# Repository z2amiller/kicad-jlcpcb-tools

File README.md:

#  KiCAD JLCPCB tools

***

***

***

Plugin to generate all files necessary for JLCPCB board fabrication and assembly

- Gerber files
- Excellon files
- BOM file
- CPL file

Furthermore it lets you search the JLCPCB parts database and assign parts directly to the footprints which result in them being put into the BOM file.

On KiCad 10 boards with named [design variants](#design-variants-kicad-10),
compare and edit variants side by side and generate separate fabrication outputs.

## Installation 💾

### KiCAD PCM

Add my custom repo to *the Plugin and Content Manager*, the URL is:

```sh
https://raw.githubusercontent.com/Bouni/bouni-kicad-repository/main/repository.json
```

From there you can install the plugin via the GUI.

### Git

Clone this repo into your KiCad `scripting/plugins` folder.

> [!TIP]
> You can open the plugins directory directly from KiCad to avoid locating the path manually:
> In the *PCB Editor*, choose **Tools → External Plugins → Open Plugin Directory** (or **Reveal Plugin Folder in Finder** on macOS), or open **Preferences → PCB Editor → Action Plugins** and click the folder icon. From that directory, open a terminal and run `git clone https://github.com/Bouni/kicad-jlcpcb-tools.git`.

Alternatively, navigate to the folder in your terminal:

**Windows (Command Prompt)**

```cmd
cd "%USERPROFILE%\Documents\KiCad\<version>\scripting\plugins"
git clone https://github.com/Bouni/kicad-jlcpcb-tools.git
```

**Windows (PowerShell)**

```powershell
cd "$HOME\Documents\KiCad\<version>\scripting\plugins"
git clone https://github.com/Bouni/kicad-jlcpcb-tools.git
```

**Linux**

```sh
cd ~/.local/share/kicad/<version>/scripting/plugins
git clone https://github.com/Bouni/kicad-jlcpcb-tools.git
```

**macOS**

```sh
cd ~/Documents/KiCad/<version>/scripting/plugins
git clone https://github.com/Bouni/kicad-jlcpcb-tools.git
```

> [!NOTE]
> `<version>` can be `7.0`, `8.0`, `9.0`, or `X.YY` depending on the version you use. You may need to create the `scripting/plugins` folder if it does not exist.

After cloning, choose **Tools → External Plugins → Refresh Plugins** in the *PCB Editor* (or restart KiCad) to load the plugin.

### Flatpak :warning:

The Flatpak installation of KiCAD currently does not ship with pip and requests installed. The later is required for the plugin to work.
In order to get it working you can run the following 3 commands:

1. `flatpak run --command=sh org.kicad.KiCad`
2. `python -m ensurepip --upgrade`
3. `/var/data/python/bin/pip3 install requests`

See [issue #94](https://github.com/Bouni/kicad-jlcpcb-tools/issues/94) for more info.

## Usage 🥳

To access the plugin choose `Tools → External Plugins → JLCPCB Tools` from the *PCB Editor* menus

Checkout this screencast, it shows quickly how to use this plugin:

### Design variants (KiCad 10+)

Create named variants in KiCad and transfer them to the PCB to use the variant
table. Boards without named variants keep the ordinary parts table.

- **Compare variants side by side**, with Ref, Footprint, Side, PCB angle, and Correction columns fixed on the left when space permits. Ref stays fixed in narrower windows.
- **Spot differences quickly** through highlighted settings and yellow outlines around the affected variant’s cells in each component row.
- **Focus on differing component settings** with **Differences only** in the toolbar above the table.
- **Edit each variant independently:** Value, LCSC assignment, and BOM/POS/POP (populated) flags. Select components within one variant for batch assignments, flag changes, and copying.
- **Copy and paste selected components between variants:** Copy transfers Value, LCSC and BOM/POS/POP settings for every selected component; select the same components in another variant and Paste. Use **Copy cell value** for an individual value, or **Copy to variants…** to choose fields and destination variants.
- **Drag variant headers to reorder them** and bring variants together for comparison.
- **Compare price and stock availability** using compact indicators and hover details.
- **Choose an Output variant** to generate its BOM, placement, and fabrication files.
- **Review placement corrections for the Output variant** in the Correction column. Exact LCSC rules follow that variant's assigned part; pattern rules use Default's reference, Value, and placed footprint.

Assignments and flags are stored in the KiCad board; save the PCB to preserve edits.

The examples below use sample component data in the main JLCPCB Tools
window. Pointer and click cues make the actions easier to follow.

#### Edit settings and see differences

Change a setting in one variant to compare it with **Default**. Here,
turning off **POP** (populated) for **R4** in **Economy** highlights the
changed cell and outlines Economy’s cells in that row. The yellow outline
remains visible while the row is selected.

Turn POP back on to match Default and clear R4’s difference highlight.

#### Show differences only

Select **Differences only** in the toolbar above the table to focus on
differing component settings. In this example, enabling the checkbox
leaves **R1** and **R3** visible. Clear it to bring all five rows back.

#### Reorder variant columns

Drag a variant header to move its entire group of columns. Here,
**Premium** moves before **Economy**.

The translucent column preview follows the pointer, while the insertion
marker and **Drop before Economy** label show the destination. Release the
header to change the order to **Default**, **Premium**, **Economy**.

## Keyboard shortcuts

Windows can be closed with ctrl-w/ctrl-q/command-w/command-w (OS dependent) and escape.
Pressing enter in the keyword text box will start a search.

### Toggle BOM / CPL attributes

You can easily toggle the `exclude from BOM` and `exclude from CPL` attributes of one or multiple footprints.

### Select LCSC parts from the JLCPCB parts database

Select one or multiple footprints, click select part. You can select parts with equal value and footprint using the Select alike button.
In the upcoming modal dialog, search for parts, select the one of your choice and click select part.
The LCSC number of your selection will then be assigned to the footprints.

To type or paste an LCSC number instead, right-click the selected footprints and choose **Enter LCSC…**. It accepts a part number such as `C25804` or a product link copied from lcsc.com or jlcpcb.com. The number may be one the downloaded parts library does not list: JLC can still assemble LCSC-only parts it buys in through pre-order or global sourcing, and your library may be older than the part. The plugin asks once before assigning such a number. With no library downloaded there is nothing to check against, so it assigns without asking.

The part selector helps the same way: search for one LCSC number, and if the results don't show that exact part, a button beside the result count assigns it with one click.

### Automatic schematic saving

Closing JLCPCB Tools saves its LCSC assignments and supported BOM settings to
the project's schematics. The manual **Export to schematic** button has been
removed. On boards with design variants, this always saves **Default**;
selecting a named variant for fabrication does not change the schematic source.

A missing assignment field preserves the schematic's existing part number;
an explicit empty assignment clears it. Invalid or conflicting assignments are
preserved and reported while safe assignments still save. Footprints are linked
to symbols by KiCad's UUID paths, so changed or duplicate references do not
redirect a save. PCB-only footprints need no schematic update. Stale or ambiguous
links are preserved and reported.
For reused sheets, a shared field is updated only when every instance is linked
and agrees on that field. A linked multi-unit component updates all authenticated
units together; incomplete or ambiguous component membership is preserved.

Ordinary unassigned parts and PCB-only footprints close quietly. If an unassigned
PCB footprint has a part number in the schematic, use KiCad's **Update PCB from
Schematic** to transfer it to the board. This is an advisory, not a save failure.
When a conflict, invalid assignment, or unresolved link needs attention, the plugin keeps the complete report
at `jlcpcb/schematic-save-report.txt`, identifying affected footprints and the
reasons. Interactive closing also shows a warning; forced shutdown saves the
report without a prompt. A later complete save removes an outdated report.
Safe partial saves can complete; they do not authorize archival of active legacy
recovery data.

Projects that already have a `jlcpcb/project.db` see a one-time notice explaining
that the schematic is now the durable store. Before the first automatic write,
the plugin also keeps a permanent zip at
`jlcpcb/schematics-before-plugin-attributes.zip` so you can restore the previous
sheets if needed.

The plugin uses the project's associated schematics and preserves an `_old`
backup for each file it writes. Projects without an associated schematic close
without writing one. If a schematic is locked, the default **Cancel** keeps the
plugin open so you can close Schematic Editor and retry. **Save Anyway** approves
only the listed locks; **Close without saving** leaves the schematic unchanged.
Save errors also let you keep the window open or close without saving the
remaining changes. Earlier sheets may already have been saved if a later write
fails. A forced application shutdown cannot wait for these prompts: locked or
failed saves are logged and the window closes.

This saves schematic files. Use KiCad's PCB save command to persist changes to
the PCB itself. An already-open Schematic Editor does not reload exported files
automatically and can overwrite them if you choose **Save Anyway**.

### Where part assignments are stored

The live KiCad board is the sole source of LCSC assignments, with or without
named design variants. Selecting, pasting, or clearing a part updates the native
footprint fields or the selected variant's fields. **Save the PCB in KiCad to
persist these changes.** Refreshing the plugin reads the current board, including
edits made outside the plugin.

Both table modes recognize `LCSC`, `JLC`, and `JLCPCB` assignment fields,
optionally followed by `Part`, `Part Number`, `Part Num`, `Part No`, `PartNr`,
`PN`, `Number`, `Code`, or `ID`; case, spaces, and punctuation are ignored.
Conflicting or invalid assignments appear unassigned. Selecting or clearing a part updates
all recognized assignment fields together. Assignments and schematic saves preserve
existing alias names. A nonempty assignment creates a hidden `LCSC` field when no
recognized alias exists. Other prefixed fields, such as `JLCPCB Rotation` or
`LCSC custom code`, remain metadata; move part numbers from such fields into a
recognized assignment field.

*KiCad Symbol Properties with sample data for a 10k 0603 resistor (C25804).*

Previously, ordinary boards used database or CSV assignments while boards with
named variants read native fields. Editing or clearing Default, then removing
the last named variant, could therefore restore an obsolete database assignment.
Both modes now read and edit the board; the former schematic/database priority
setting no longer applies.

On opening, the plugin checks an existing `jlcpcb/project.db` for recoverable
legacy assignments before applying part preferences or displaying the initial
BOM. It imports a valid LCSC number only when the board assignment field is
missing and the reference, value, footprint, and BOM/POS flags exactly match
the historical row. Every linked schematic unit must also have no assignment or
the same part number. PCB-only footprints and projects confirmed to have no
schematic can recover directly into native fields, even if the PCB retains old
symbol paths. Unreadable project files and missing declared sheets do not count
as an absent schematic. KiCad 10's generated placeholder for a layout-only
project does not require a schematic file. Within a discovered hierarchy, stale
or ambiguous links remain unresolved.
Existing native values, explicit clears, invalid or conflicting
fields, unresolved links, and disagreeing shared instances are preserved.
Recovery imports neither stock nor flags and does not require a parts catalog.
Save the PCB to retain recovered assignments.

Once recovery is durable in the saved schematic or PCB, the active `part_info`
table is renamed to `part_info_retired`, preserving its rows and schema. Existing
archives remain intact; later archives use names such as `part_info_retired_2`.
The plugin rechecks the table's schema and data inside the archive transaction
so another window's changes cannot be archived using an outdated recovery check.
Before archival, the plugin reads the saved current PCB and sibling PCBs in the
same directory. macOS AppleDouble metadata sidecars are excluded. Recovery needed
by another board stays active, including recovery needed by temporary PCB copies.
The migration report names blocking sibling files and repeats only new notices;
acknowledgment does not allow archival. Obsolete rows can
be archived only when those saved boards confirm they are no longer needed;
an unsaved deletion or footprint change is insufficient. Native-only recovery
stays active until you explicitly save the PCB. The plugin never saves it for
you. Cancellation, incomplete saves, unresolved recovery, and unreadable saved
boards retain the recovery table for a later retry.

The durable `jlcpcb/legacy-migration-report.json` records the source board, old
legacy value, chosen native value or clear, and the reason for each recovery
decision, retaining original provenance and the latest board snapshot without
adding a full snapshot for every session. It survives schematic-report cleanup
and archival. When an existing native value or explicit clear supersedes a
legacy number, an interactive close
shows the previously unseen decisions once. Forced shutdown leaves that notice
pending for the next interactive close. Failed audit writes retain recovery data
and retry later without reapplying imported assignments. If the audit still cannot
be written, keep the plugin open to retry. Explicitly closing without the audit
or forcing shutdown can lose observations that could not be written to disk.

Archived assignments are never imported again, and legacy CSV files are never
automatically imported. Archival preserves generation counters, corrections,
other tables, and CSV files. Reading or refreshing assignments does not create
or modify `part_info`; the notice acknowledgment and generation counter use
the separate `metadata` table.

Supplier descriptions and other part details are cached in memory by LCSC
number and fetched again as needed. A part's assembly process and
Standard-only class are the exception: they are saved by LCSC number in
`global.db` in the data folder, so a board opened again shows them at once,
and they are fetched again in the background once they are 30 days old.
Stock and pricing come from the currently selected parts catalog; they are
not persisted as board assignments.

### Part preferences

Part preferences remember which LCSC part to use for a value and footprint combination across projects. Two independent settings are enabled by default:

- **Remember my part preferences** remembers each successful part selection or pasted LCSC assignment. The latest explicit assignment replaces the preference; opening a board does not change preferences.
- **Parts preferences fill in empty LCSC assignments** fills blank LCSC assignments once each time the plugin window opens. Existing assignments are preserved. DNP parts and parts excluded from BOM or POS are skipped.

Applying part preferences, including automatic filling on opening, writes the
native board fields. Save the PCB to keep those assignments.

Clearing an LCSC assignment keeps its part preference, so an eligible blank assignment may fill again on the next opening. Exclude the part or disable automatic filling to keep it blank. The right-click actions **Save part preferences** and **Apply part preferences** remain available even when automation is disabled. Use **Part preferences** to delete, import, or export preferences. Deleting a preference does not remove assignments from your boards.

### Generate fabrication data

Generate all necessary assembly files for your board with a simple click.

A new directory called `jlcpcb` is created, and in there, two separate folders are created, `gerber` and `production_files`.

In the gerber folder all necessary `*.gbr` and `*.drl` files are generated and zipped into the `production_files` folder, ready for upload to JLCPCB.
The zipfile is named `GERBER-<projectname>.zip`

Also in the `production_files` folder, two files are generated, `BOM-<projectname>.csv` and `CPL-<projectname>.csv`.

Footprints are included into the BOM and CPL files according to their `exclude from BOM` and `exclude from POS` attributes.

A footprint's CPL `Mid X`/`Mid Y` is the center of the bounding box of its soldered pads: NPTH holes and paste-only pads are left out, and a footprint without soldered pads uses its own position.

Optional pre/post generation hook scripts can be configured in settings.

- The pre-hook runs before generation and can block generation on failure (with Continue/Cancel prompt).
- The post-hook runs only after successful generation.

See [HOOKS.md](HOOKS.md) for configuration details and available environment variables.

### Export Additional JLC Specific Layers

Some boards you have manufactured will require additional layers in your Gerber. For example, when manufacturing flex PCBs with a stiffener, JLC requires a layer outlining the stiffener layer (top/bottom), dimensions and the stiffener material properties (material, thickness etc). Export these additional JLC specific layers in your production files with a simple modification.

Additional layers can be exported by creating layers with `JLC_` as the prefix of the layer name. You can access and edit the layer names in *Board Setup/Board Stackup/Board Editor Layers*

This tool will automatically export all additional layers with the JLC_ prefix and add them to the production files in `GERBER-<projectname>.zip`

## Footprint rotation correction

JLCPCB seems to need corrected rotation information. @matthewlai implemented that in his [JLCKicadTools](https://github.com/matthewlai/JLCKicadTools) and I adopted his work in this plugin as well.
You can download Matthews file from GitHub and manage your own corrections in the Rotation manager.

See [Importing and repairing corrections](CORRECTIONS.md) for supported CSV
formats, validation rules, and recovery of invalid records from older versions.

## Icons

This plugin makes use of a lot of icons from the excellent [Material Design Icons](https://materialdesignicons.com/)

## Development

1. Fork repo
2. Git clone forked repo
3. Install pre-commit `pip install pre-commit`
4. Setup pre-commit `pre-commit run`
5. Create feature branch `git switch -c my-awesome-feature`
6. Make your changes
7. Commit your changes `git commit -m "Awesome new feature"`
8. Push to GitHub `git push`
9. Create PR

Make sure you make use of pre-commit hooks in order to format everything nicely with `black`
In the near future I'll add `ruff` / `pylint` and possibly other pre-commit-hooks that enforce nice and clean code style.

### Tests

Report ordinary Python tests, real wx controls, and real KiCad tests separately.
A passing test that uses a fake board does not verify KiCad's file handling,
project state, or native object cleanup.

```sh
python -m pytest -rs -m 'not native_wx and not native_kicad'
python -m pytest -rs --require-native=wx -m 'not native_kicad and not os_input'
python -m pytest -rs --require-native=wx -m os_input
python -m pytest -rs --require-native=kicad -m native_kicad
```

The required native modes reject missing libraries, empty native selections, and
skipped native tests. The KiCad mode accepts two skips: tests of design variants on
a KiCad without them, and the forced-DRC test on KiCad 10, whose DRC crashes
outside KiCad. Run them with Python libraries matching the installed KiCad
or wx packages. Mouse/keyboard tests require an isolated desktop with a window
manager; Linux native tests can use Xvfb.

To reproduce CI locally, use an Ubuntu 24.04 Docker container with the same CPU
architecture, KiCad packages, dependencies, and commands as
[the test workflow](.github/workflows/tests.yml). Copy the tracked source tree so
untracked test files cannot change collection. Include the tested revision,
Python/wx/KiCad versions, command, and pass/skip/deselection counts when reporting
results. A required lane that was not run remains unvalidated.

### Settings

`default_settings.json` holds the settings a fresh install starts from and is the only
settings file tracked in git. The plugin writes the settings you actually use to
`settings.json` beside it, which is git-ignored, so toggling a checkbox while developing
no longer shows up as a change to commit.

On every launch the stored settings are layered over the defaults, so a setting added by
a newer version arrives with its default rather than being missing. Add new settings to
`default_settings.json`; `tests/test_settings_defaults.py` fails if a setting the code
reads has no default shipped for it.

## How to rebuild the parts database

The parts database is rebuilt by the [update_parts_database.yml GitHub workflow](https://github.com/Bouni/kicad-jlcpcb-tools/blob/main/.github/workflows/update_parts_database.yml)

You can reference the steps in the 'Update database' section for the commands to run locally.

## python libraries

lib/ contains the necessary python packages that may not be a part of the KiCad python distribution.

These packages include:

- packaging

To install a package, such as 'packaging':

```python
pip install packaging --target ./lib
```

To update these packages:

```python
pip install packaging --upgrade --target ./lib
```

Future versions of KiCad may have support for a requires.txt to automate this process.

## Standalone mode

Allows the plugin UI to be started without KiCAD, enabling debugging with an IDE like pycharm / vscode.

Standalone mode is under development.

### Limitations

- All board / footprint / value data are hardcoded stubs, see standalone_impl.py

### How to use

To use the plugin in standlone mode you'll need to identify three pieces of information specific to your Kicad version, plugin path, and OS.

#### Python

The <i><b>{KiCad python}</b></i> should be used, this can be found at different locations depending on your system:

| OS     | Kicad python                                                                                |
|--------|---------------------------------------------------------------------------------------------|
|Mac     | /Applications/KiCad/KiCad.app/Contents/Frameworks/Python.framework/Versions/3.9/bin/python3 |
|Linux   | /usr/bin/python3                                                                            |
|Windows | C:\Program Files\KiCad\8.0\bin\python.exe                                                   |

#### Working directory

The <i><b>{working directory}</b></i> should be your plugins directory, ie:

| OS     | Working dir                                                |
|--------|------------------------------------------------------------|
|Mac     | ~/Documents/KiCad/<version>/scripting/plugins/             |
|Linux   | ~/.local/share/kicad/<version>/scripting/plugins/          |
|Windows | %USERPROFILE%\Documents\KiCad\<version>\scripting\plugins\ |

> [!NOTE]  
> <version> can be 7.0, 8.0, 9.0, or X.YY depending on the version you use

#### Plugin folder name

The <i><b>{kicad-jlcpcb-tools folder name}</b></i> should be the name of the kicad-jlcpcb-tools folder.

- For Kicad managed plugins this may be like

> com_github_bouni_kicad-jlcpcb-tools

- If you are developing kicad-jlcpcb-tools this is the folder you cloned the kicad-jlcpcb-tools as.

#### Command line

- Change to the working directory as noted above
- Run the python interpreter with the <i><b>{kicad-jlcpcb-tools folder name}</b></i> folder as a module.

For example:

```sh
cd {working directory}
{kicad_python} -m {kicad-jlcpcb-tools folder name}
```

For example on Mac:

```sh
/Applications/KiCad/KiCad.app/Contents/Frameworks/Python.framework/Versions/3.9/bin/python3 -m kicad-jlcpcb-tools
```

For example on Linux:

```sh
cd ~/.local/share/kicad/8.0/scripting/plugins/ && python -m kicad-jlcpcb-tools
```

For example on Windows:

```cmd
& 'C:\Program Files\KiCad\8.0\bin\python.exe' -m kicad-jlcpcb-tools
```

#### IDE

- Configure the command line to be '{kicad_python} -m {kicad-jlcpcb-tools folder name}'
- Set the working directory to {working directory}

If using PyCharm or Jetbrains IDEs, set the interpreter to Kicad's python, <i><b>{Kicad python}</b></i> and under 'run configuration' select Python.

Click on 'script path' and change instead to 'module name',
entering the name of the kicad-jlcpcb-tools folder, <i><b>{kicad-jlcpcb-tools folder name}</b></i>.

## How to release new versions of this plugin

[bouni-kicad-repository](https://raw.githubusercontent.com/Bouni/bouni-kicad-repository/main/repository.json) contains the
files for the latest version of the plugin, in the format KiCAD expects from external plugins.

To release a new version of this plugin:

1. In the <b>kicad-jlcpcb-plugin</b> repository:
   1. Visit the releases page 
   1. Click on 'Choose a tag', enter the next release number, say 2025.04.01 for example, and click on 'Create Tag' 
   1. Click 'Generate release notes' 
   1. If the release notes looks good, click on 'Publish release' 
1. Automatically the new release will trigger the 'kicad-pcm' workflow which will:
   1. Pull the latest plugin tag
   1. Create the appropriate pcm archive
   1. Upload the zip as an asset to a new GitHub release
   1. benc-uk/workflow-dispatch@v1 is used to trigger the 'Rebuild repository' workflow in [bouni-kicad-repository](https://github.com/Bouni/bouni-kicad-repository)
1. Automatically in the <b>bouni-kicad-repository</b>, the 'Rebuild repository' (rebuild.yml) workflow runs 'generate.py'
   1. generate.py updates .json and the latest .zip file using the release assets from the kicad-jlcpcb-plugin repository
1. The plugin should now be visible to users via the plugin manager.

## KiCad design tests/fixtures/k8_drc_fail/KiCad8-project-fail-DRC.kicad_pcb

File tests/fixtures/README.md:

# KiCad SWIG integration fixtures

This folder holds small board fixtures used by `pytest -m kicad_integration`.

## Fixture goals

- Keep fixtures small and quick to parse in CI.
- Prefer representative real-world examples when practical.
- Include one intentionally DRC-failing board for stable-path/category assertions.

## Version compatibility policy

- Primary compatibility test direction: **KiCad 8 board opened in KiCad 9 runtime**.
- Reverse compatibility (KiCad 9 board in KiCad 8 runtime) is not required.

## Suggested fixture set

- `k9_smoke_ok/` – small KiCad 9 board that loads cleanly.
- `k9_drc_fail/` – small KiCad 9 board with intentional DRC issues.
- `k8_compat_ok/` – KiCad 8 board expected to open in KiCad 9 runtime.

## Current checked-in fixtures

- `k9_smoke_ok/fx-Full125B.kicad_pcb` – initial real-world KiCad 9 smoke fixture.
- `k9_drc_fail/Normal125B-DRCFail.kicad_pcb` – real-world KiCad 9 fixture intended to fail DRC.
- `k8_compat_ok/KiCad8-project.kicad_pcb` – KiCad 8 board for open-in-KiCad-9 compatibility checks.
- `k8_drc_fail/KiCad8-project-fail-DRC.kicad_pcb` – KiCad 8 board intended to fail DRC checks.
- `k10_smoke_ok/util-curvetracer.kicad_pcb` – KiCad 10 smoke fixture (native KiCad 10 runtime).
- `k10_drc_fail/util-curvetracer-fail-drc.kicad_pcb` – KiCad 10 DRC-fail fixture.

Fixture metadata is tracked in `tests/fixtures/manifest.json` and consumed by integration tests.

### Manifest conventions

- `intent: "smoke_ok"` for basic load/enumeration fixtures.
- `intent: "compat_open_in_k9"` for cross-version open tests (e.g. KiCad 8 -> KiCad 9).
- `intent: "drc_fail"` for intentional DRC-failing fixtures.
- `expected_drc_patterns` can optionally list stable substrings that should appear in parsed DRC error messages.
- `min_runtime_major` / `max_runtime_major` can constrain fixtures to matching KiCad runtimes.

### DRC integration execution

DRC integration checks are opt-in by default. Enable them with:

```sh
KICAD_DRC_INTEGRATION=1 pytest -m kicad_integration tests/test_kicad_swig_integration.py
```

## Notes

- Store only non-sensitive board data.
- Keep external dependencies out of fixture projects where possible.
- If exact DRC violation counts drift by KiCad version, tests should assert stable categories/paths instead of exact totals.

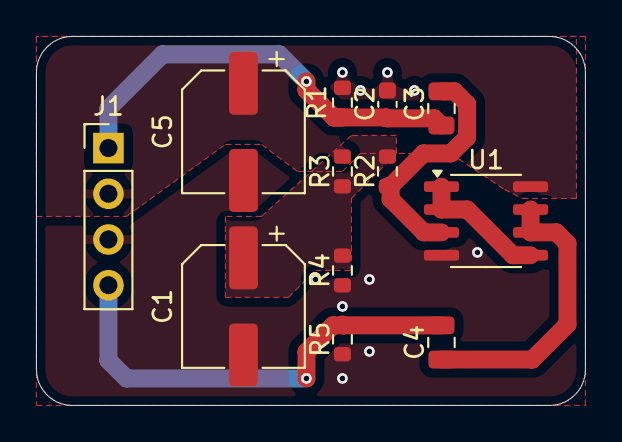
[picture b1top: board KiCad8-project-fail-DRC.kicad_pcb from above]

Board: 2 copper layers, 30.5 x 20.5 mm, 12 parts (0 on the bottom side), 8 nets.

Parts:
C1, C5: 100uF; CP_Elec_6.3x4.5
C2: 100pF; C_0603_1608Metric
C3: 100nF; C_0805_2012Metric
C4: 1uF; C_0805_2012Metric
J1: Conn_01x04_Pin; PinHeader_1x04_P2.54mm_Vertical
R1: 2.2M; R_0603_1608Metric
R2: 470K; R_0603_1608Metric
R3, R4: 47K; R_0603_1608Metric
R5: 100K; R_0603_1608Metric
U1: TL072; SOIC-8_3.9x4.9mm_P1.27mm

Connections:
+9V: C5.1, J1.2, R3.1, U1.8 (V+)
GND: C1.2, C2.2, C5.2, J1.3, R1.2, R4.2, R5.2, U1.4 (V-)
IN: C2.1, C3.2, J1.1, R1.1
unnamed: C3.1, R2.2, U1.3 (+)
unnamed: U1.1, U1.2 (-), U1.5 (+)
unnamed: C4.2, U1.6 (-), U1.7
OUT: C4.1, J1.4, R5.1
VREF: C1.1, R2.1, R3.2, R4.1

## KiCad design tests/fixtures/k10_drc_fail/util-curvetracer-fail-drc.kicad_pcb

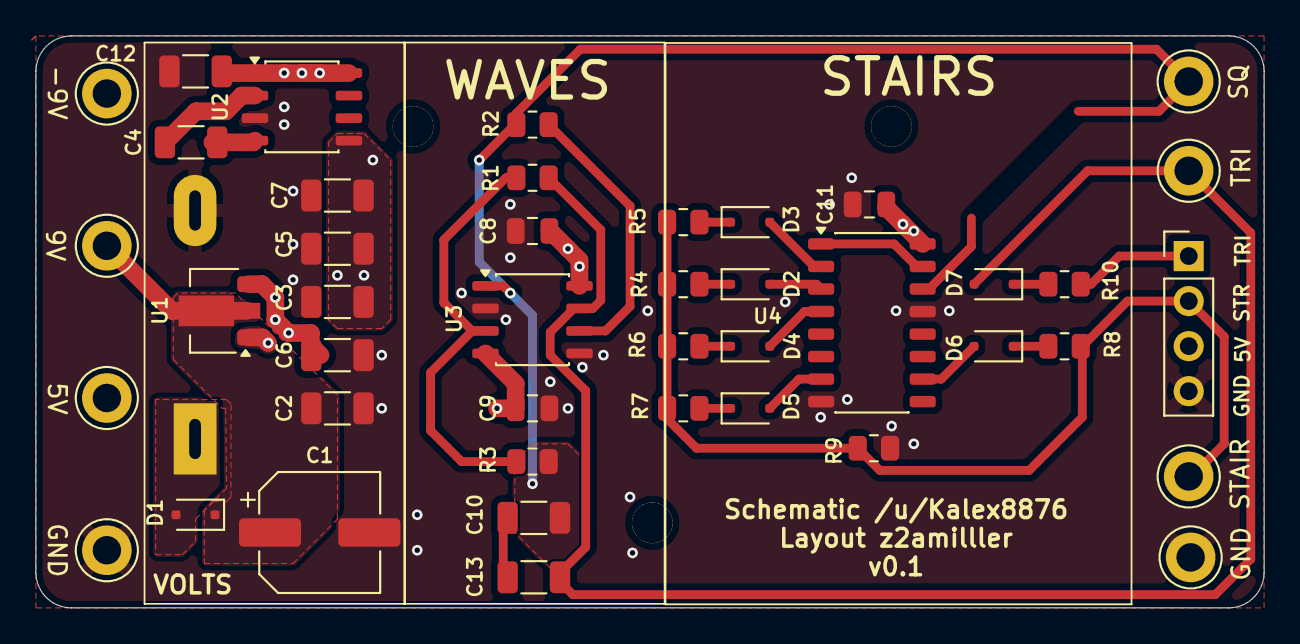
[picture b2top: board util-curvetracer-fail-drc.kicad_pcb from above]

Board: 4 copper layers, 69.2 x 32.2 mm, 44 parts (1 on the bottom side), 26 nets.

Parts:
BT1: Battery_Cell; BatteryHolder_MPD_BA9VPC_1xPP3
C1: 100uF; CP_Elec_6.3x5.4
C2, C3, C4, C5, C6, C7, C10, C12, C13: 10uF; C_1206_3216Metric
C8, C9, C11: 1uF; C_0805_2012Metric
D1: 1N5819; D_SOD-323F
D2, D3, D4, D5, D6, D7: 5S30; D_SOD-323F
J1: Conn_01x04_Socket; PinHeader_1x04_P2.54mm_Vertical
R1: 10K; R_0805_2012Metric
R2, R7, R10: 1K; R_0805_2012Metric
R3: 20K; R_0805_2012Metric
R4: 7.5K; R_0805_2012Metric
R5: 3.6K; R_0805_2012Metric
R6: 1.8K; R_0805_2012Metric
R8: 560R; R_0805_2012Metric
R9: 1.2K; R_0805_2012Metric
TP1: 9V; TestPoint_Keystone_5010-5014_Multipurpose
TP2: 5V; TestPoint_Keystone_5010-5014_Multipurpose
TP3, TP8: GND; TestPoint_Keystone_5010-5014_Multipurpose
TP4: -9V; TestPoint_Keystone_5010-5014_Multipurpose
TP5: SQ; TestPoint_Keystone_5010-5014_Multipurpose
TP6: TRI; TestPoint_Keystone_5010-5014_Multipurpose
TP7: STAIR; TestPoint_Keystone_5010-5014_Multipurpose
U1: HT75xx-1-SOT89; SOT-89-3
U2: LTC1044; JEITA_SOIC-8_3.9x4.9mm_P1.27mm
U3: TL072; JEITA_SOIC-8_3.9x4.9mm_P1.27mm
U4: 4017; JEITA_SOIC-16_3.9x9.9mm_P1.27mm

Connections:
+5V: C3.1, C11.1, J1.3, TP2.1 (1_1), U1.3 (VOUT), U4.16 (VDD)
+9V: BT1.1 (+), D1.2 (A)
+9VA: C1.1, C2.1, C8.1, C12.1, D1.1 (K), TP1.1 (1_1), U1.2 (VIN), U2.1 (BOOST), U2.8 (V+), U3.8 (V+)
-9V: C5.1, C6.1, C7.1, C9.2, TP4.1 (1_1), U2.5 (VOUT), U3.4 (V-)
GND: BT1.2 (-), C1.2, C2.2, C3.2, C5.2, C6.2, C7.2, C8.2, C9.1, C11.2, C12.2, J1.4, R9.2, TP3.1 (1_1), TP8.1 (1_1), U1.1 (GND), U2.3 (GND), U3.2 (-), U3.5 (+), U4.8 (VSS), U4.13 (CKEN)
unnamed: C10.1, C13.2
unnamed: D2.2 (A), U4.3 (Q0)
unnamed: D2.1 (K), R4.1
unnamed: D3.2 (A), U4.2 (Q1)
unnamed: D3.1 (K), R5.1
unnamed: D4.2 (A), U4.4 (Q2)
unnamed: D4.1 (K), R6.1
unnamed: D5.2 (A), U4.7 (Q3)
unnamed: D5.1 (K), R7.1
unnamed: D6.2 (A), U4.10 (Q4)
unnamed: D6.1 (K), R8.1
unnamed: D7.1 (K), R10.2
unnamed: J1.1, R10.1
unnamed: C4.1, U2.2 (CAP+)
unnamed: C4.2, U2.4 (CAP-)
unnamed: R1.2, R3.2, U3.3 (+)
unnamed: R2.1, U3.6 (-)
unnamed: U4.1 (Q5), U4.15 (Reset)
SQUARE: C10.2, R2.2, R3.1, TP5.1 (1_1), U3.1, U4.14 (CLK)
STAIRCASE: J1.2, R4.2, R5.2, R6.2, R7.2, R8.2, R9.1, TP7.1 (1_1)
TRIANGLE: C13.1, D7.2 (A), R1.1, TP6.1 (1_1), U3.7

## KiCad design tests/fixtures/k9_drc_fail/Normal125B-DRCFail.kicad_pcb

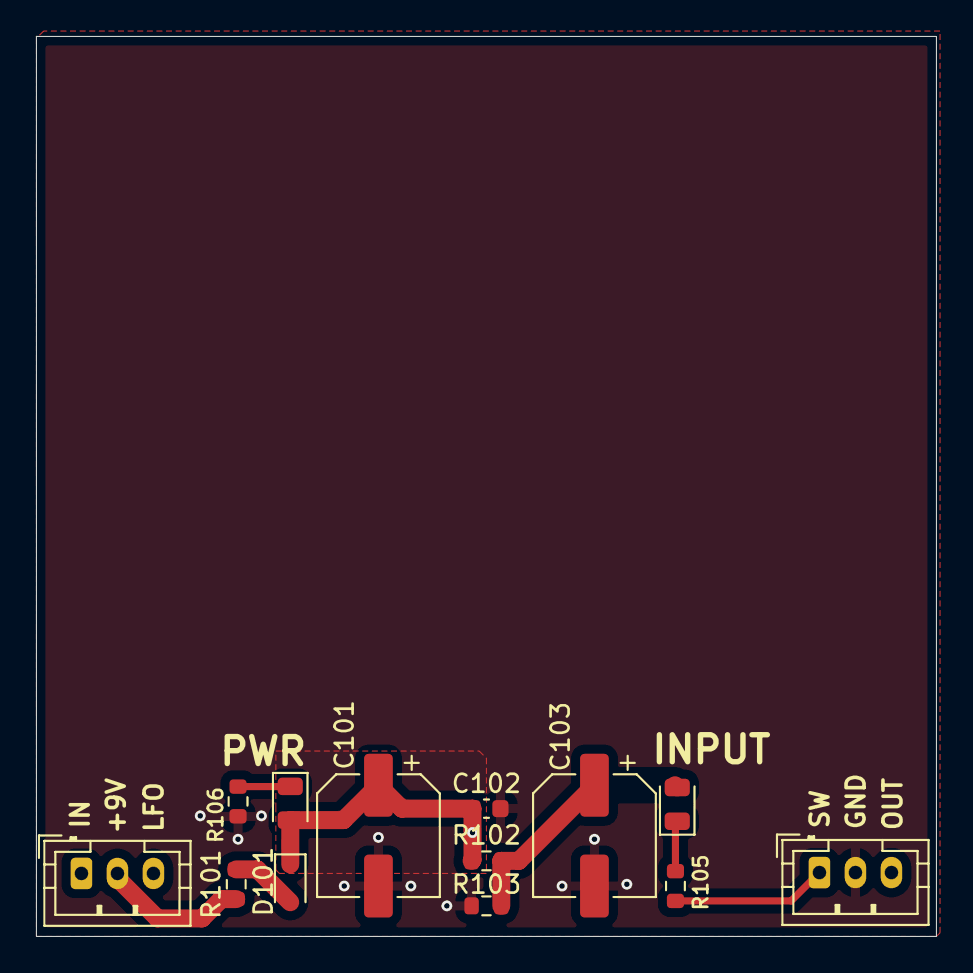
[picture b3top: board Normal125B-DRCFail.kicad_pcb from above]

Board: 2 copper layers, 50.0 x 50.0 mm, 13 parts (0 on the bottom side), 8 nets.

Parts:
C101: 100uF; CP_Elec_6.3x5.9
C102: 100nF; C_0603_1608Metric
C103: 100uF; CP_Elec_6.3x9.9
D101: 1N5819; D_SOD-323
D103, D104: LED; LED_0805_2012Metric
J101, J102: Conn_01x03_Socket; JST_PH_B3B-PH-K_1x03_P2.00mm_Vertical
R101: 10R; R_0603_1608Metric
R102, R103, R106: 10k; R_0603_1608Metric
R105: 4.7K; R_0603_1608Metric

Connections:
+9V: J101.2, R101.2
+9VA: C101.1, C102.1, D101.1 (K), D104.2 (A), R102.1
/Board Basic Setup/INT_PWR_LED: D104.1 (K), R106.1
/Board Basic Setup/INT_SWITCH_LED: D103.1 (K), R105.1
GND: C101.2, C102.2, C103.2, J102.2, R103.2, R106.2
unnamed: D101.2 (A), R101.1
SWITCH: J102.1, R105.2
VREF: C103.1, D103.2 (A), R102.2, R103.1
